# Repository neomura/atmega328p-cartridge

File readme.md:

# neomura/atmega328p-cartridge

Circuit design and games engine for ATMega328P-based cartridges for the Neomura retro games console.

Derived from the [Arduinocade project](https://github.com/rossumur/Arduinocade).

| Link                                         | Description                                                                         |
| -------------------------------------------- | ----------------------------------------------------------------------------------- |
| [License](./license.md)                      | MIT License.                                                                        |
| [Documentation](./documentation/readme.md)   | Documentation regarding this project.                                               |
| [Circuit Design](./circuit-design/readme.md) | KiCad files and assembly instructions for the PCB.                                  |
| [Engine](./engine/readme.md)                 | Source code for the games engine.                                                   |
| [Palette](./palette.aseprite)                | Aseprite palette; each group of four colors is an available palette for a scanline. |

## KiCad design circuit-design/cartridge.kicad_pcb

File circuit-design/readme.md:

# [neomura/atmega328p-cartridge](../readme.md)/Circuit Design

| Link                                         | Description                        |
| -------------------------------------------- | ---------------------------------- |
| [cartridge.pro](./cartridge.pro)             | KiCAD project.                     |
| [cartridge.sch](./cartridge.sch)             | KiCAD schematic.                   |
| [cartridge.kicad_pcb](./cartridge.kicad_pcb) | KiCAD PCB layout.                  |

## Bill of materials

Links are included for reference only and are not endorsements.

| Reference   | Description                                                          | Model No.         | Link                                                                                                                                                                                               |
| ----------- | -------------------------------------------------------------------- | ----------------- | -------------------------------------------------------------------------------------------------------------------------------------------------------------------------------------------------- |
| J1          | Cartridge connector (right-angled 1x15 2.54mm male pin header)       | Unknown           | [https://www.aliexpress.com/item/4000660389713.html?spm=a2g0s.9042311.0.0.65b74c4dMpBmdG](https://www.aliexpress.com/item/4000660389713.html?spm=a2g0s.9042311.0.0.65b74c4dMpBmdG)                 |
| J2          | ICSP header (right-angled 1.5 2.54mm male pin header)                | Unknown           | [https://www.bitsbox.co.uk/index.php?main_page=product_info&cPath=225_230&products_id=3128](https://www.bitsbox.co.uk/index.php?main_page=product_info&cPath=225_230&products_id=3128)             |
| U1          | Microcontroller                                                      | ATMega328P-PU     | [https://www.bitsbox.co.uk/index.php?main_page=product_info&cPath=140_161_162&products_id=1225](https://www.bitsbox.co.uk/index.php?main_page=product_info&cPath=140_161_162&products_id=1225)     |
| X1          | 14.31818MHz (NTSC) or 17.734MHz (PAL 60) HC-49S crystal              | Unknown           | [https://www.aliexpress.com/item/32496964768.html?spm=a2g0s.9042311.0.0.65b74c4dMpBmdG](https://www.aliexpress.com/item/32496964768.html?spm=a2g0s.9042311.0.0.65b74c4dMpBmdG) or [https://www.ebay.co.uk/itm/20pcs-17-734MHz-HC-49S-Crystal-Oscillator-Passive-Quartz-Resonator/253056403948?_trkparms=aid%3D111001%26algo%3DREC.SEED%26ao%3D1%26asc%3D20160908105057%26meid%3D80fd100fd3114f5ba72a3c52a978bf7f%26pid%3D100675%26rk%3D1%26rkt%3D15%26mehot%3Dnone%26sd%3D253056403948%26itm%3D253056403948%26pmt%3D1%26noa%3D1%26pg%3D2380057%26brand%3DUnbranded&_trksid=p2380057.c100675.m4236&_trkparms=pageci%3Ae010b98a-7b73-11eb-b850-3214b911b9a1%7Cparentrq%3Af3c20fd51770a7b3a0b1a3e8fffcf90a%7Ciid%3A1](https://www.ebay.co.uk/itm/20pcs-17-734MHz-HC-49S-Crystal-Oscillator-Passive-Quartz-Resonator/253056403948?_trkparms=aid%3D111001%26algo%3DREC.SEED%26ao%3D1%26asc%3D20160908105057%26meid%3D80fd100fd3114f5ba72a3c52a978bf7f%26pid%3D100675%26rk%3D1%26rkt%3D15%26mehot%3Dnone%26sd%3D253056403948%26itm%3D253056403948%26pmt%3D1%26noa%3D1%26pg%3D2380057%26brand%3DUnbranded&_trksid=p2380057.c100675.m4236&_trkparms=pageci%3Ae010b98a-7b73-11eb-b850-3214b911b9a1%7Cparentrq%3Af3c20fd51770a7b3a0b1a3e8fffcf90a%7Ciid%3A1) |
| R1          | 1M load resistor                                                     | Unknown           | [https://www.bitsbox.co.uk/index.php?main_page=product_info&cPath=83_84_85&products_id=480](https://www.bitsbox.co.uk/index.php?main_page=product_info&cPath=83_84_85&products_id=480)             |
| C1/C2       | 22pF load capacitor                                                  | Unknown           | [https://www.bitsbox.co.uk/index.php?main_page=product_info&cPath=65_75_67&products_id=187](https://www.bitsbox.co.uk/index.php?main_page=product_info&cPath=65_75_67&products_id=187)             |
| D1          | Reset protection diode                                               | 1N4148            | [https://www.bitsbox.co.uk/index.php?main_page=product_info&cPath=140_141_143&products_id=925](https://www.bitsbox.co.uk/index.php?main_page=product_info&cPath=140_141_143&products_id=925)       |
| R2          | 4.7k reset pull-up resistor                                          | Unknown           | [https://www.bitsbox.co.uk/index.php?main_page=product_info&cPath=83_84_85&products_id=452](https://www.bitsbox.co.uk/index.php?main_page=product_info&cPath=83_84_85&products_id=452)             |
| C3          | 100nF reset bypass capacitor                                         | Unknown           | [https://www.bitsbox.co.uk/index.php?main_page=product_info&cPath=65_75_67&products_id=210](https://www.bitsbox.co.uk/index.php?main_page=product_info&cPath=65_75_67&products_id=210)             |
| C4          | 100nF +5V bypass capacitor                                           | Unknown           | [https://www.bitsbox.co.uk/index.php?main_page=product_info&cPath=65_75_67&products_id=210](https://www.bitsbox.co.uk/index.php?main_page=product_info&cPath=65_75_67&products_id=210)             |
| R3          | 470R video carrier resistor                                          | Unknown           | [https://www.bitsbox.co.uk/index.php?main_page=product_info&cPath=83_84_85&products_id=441](https://www.bitsbox.co.uk/index.php?main_page=product_info&cPath=83_84_85&products_id=441)             |
| R4          | 1K video sync resistor                                               | Unknown           | [https://www.bitsbox.co.uk/index.php?main_page=product_info&cPath=83_84_85&products_id=445](https://www.bitsbox.co.uk/index.php?main_page=product_info&cPath=83_84_85&products_id=445)             |
| R5/R7       | 270R audio low-pass resistor                                         | Unknown           | [https://www.bitsbox.co.uk/index.php?main_page=product_info&cPath=83_84_85&products_id=438](https://www.bitsbox.co.uk/index.php?main_page=product_info&cPath=83_84_85&products_id=438)             |
| C5/C7       | 33nF audio low-pass capacitor                                        | Unknown           | [https://www.bitsbox.co.uk/index.php?main_page=product_info&cPath=65_75_67&products_id=208](https://www.bitsbox.co.uk/index.php?main_page=product_info&cPath=65_75_67&products_id=208)             |
| R6/R8       | 150R audio output resistor                                           | Unknown           | [https://www.bitsbox.co.uk/index.php?main_page=product_info&cPath=83_84_85&products_id=435](https://www.bitsbox.co.uk/index.php?main_page=product_info&cPath=83_84_85&products_id=435)             |
| C6/C8       | 10uF audio output capacitor                                          | Unknown           | [https://www.amazon.co.uk/gp/product/B08D647KCD/ref=ppx_yo_dt_b_asin_title_o00_s00?ie=UTF8&psc=1](https://www.amazon.co.uk/gp/product/B08D647KCD/ref=ppx_yo_dt_b_asin_title_o00_s00?ie=UTF8&psc=1) |

### Possible substitutions

#### J1

Right-angled male pin headers appear to come in two distinct styles; one where the plastic retainer is in contact with the PCB, and one where it is instead in contact with the corresponding female socket.  This PCB is designed for the latter, and the former will not fit inside a cartridge shell.

#### J2

In contrast to J1, this must be the style with the plastic retainer in contact with the PCB to fit inside a cartridge shell.  This can be substituted for a vertical pin header (or a socket) if it does not need to fit inside a cartridge shell.

#### U1

Other pin-compatible ATMega ICs may work.  Note that most will have smaller flash space and may not be able to store complex games.

#### X1/R1/C1/C2

Most 14.31818MHz crystals which are HC49 or smaller will work as long as appropriate bypass capacitors and resistor are included.  To be compatible with Arduinocade games instead of Neomura games, a 28.6363MHz crystal such as [https://www.aliexpress.com/item/32910067235.html?spm=a2g0s.9042311.0.0.5bfd4c4d3a2EOO](https://www.aliexpress.com/item/32910067235.html?spm=a2g0s.9042311.0.0.5bfd4c4d3a2EOO) may be used instead.

It may be possible to omit the load resistor.

#### D1

This diode is included to prevent accidental high-voltage programming.  It can be omitted.

## Assembly instructions

- Start by soldering J1 and J2.  I would recommend using some kind of clamp such as a crocodile clip to keep it firmly attached to the board (note that it will act as a heatsink, making soldering more difficult, if in contact with pins).  Use short bursts of high heat and allow time to cool between joints to avoid melting the plastic retainer.  After soldering, use a female socket to ensure that pins are straight, and use said female socket to correct the pins if not parallel with the PCB.
- Solder all other components.  There is not much room inside the shell once constructed, so ensure that these are as close to the board top as possible and that leads are clipped short.
- Place the PCB, logo up, into the back half of the shell.
- Place the front half of the shell on top and press fit.  Be careful to ensure that no components will be crushed, such as C1 and C2; you may need to stand these at 45 degrees to avoid contact with the front half of the case.

### Program

J2 is all pins except VCC of a standard 2x3 ICSP header.  These have been arranged to match pins 10-13 of an Arduino used as a programmer.

If using an [Arduino as an ISP](https://www.arduino.cc/en/Tutorial/BuiltInExamples/ArduinoISP), connect the following pins (where the Arduino has multiple pins labelled the same, any will work):

| Arduino | ICSP  |
| ------- | ----- |
| GND     | GND.  |
| 5V      | VCC.  |
| 13      | SCK.  |
| 12      | MISO. |
| 11      | MOSI. |
| 10      | RST.  |

#### Set fuse bits

By default, an ATMega328P will use its internal 8MHz clock rather than an external crystal.  To configure this, use [AVRDUDE](https://www.nongnu.org/avrdude/) to set the correct fuse bits:

```shell
avrdude -pM328P -Ulfuse:w:0xf7:m -Uhfuse:w:0xde:m -Uefuse:w:0xfd:m
```

Note that you will need to add command line arguments to this to specify which programmer you are using, for example:

| Programmer                                 | Suffix                         |
| ------------------------------------------ | ------------------------------ |
| USBtiny                                    | -cusbtiny                      |
| Arduino as ISP on COM port 3 under Windows | -cavrisp -b 19200 -Pcom3       |
| Arduino as ISP on COM port 3 under Linux   | -cavrisp -b 19200 -P/dev/ttyS3 |

If you are running AVRDUDE under Windows Subsystem for Linux, you may find that the remapped COM ports do not work.  In these instances, running AVRDUDE under Windows at least once seems to resolve this.

You may see an error that the extended fuse could not be written.  This is normal, as not all of its bits are writable; it could be argued to be more of an AVRDUDE bug that it tried to check them.

#### Flash

Next, write a program to flash.  Make sure that a .hex file to write exists in the current working directory, then execute:

```shell
avrdude -pM328P -Uflash:w:name-of-your-hex-file.hex
```

As before, you will need to add command line arguments to specify the correct programmer.

After following these steps, you should be able to connect the video pin (cartridge left 1) to the composite video input on a NTSC-compatible display and see a picture.

## References

| Link                                                                                                                                                     | Description                            |
| -------------------------------------------------------------------------------------------------------------------------------------------------------- | -------------------------------------- |
| [https://www.instructables.com/Adding-ICSP-header-to-your-ArduinoAVR-board/](https://www.instructables.com/Adding-ICSP-header-to-your-ArduinoAVR-board/) | Source for ICSP header layout.         |
| [https://www.arduino.cc/en/Tutorial/BuiltInExamples/ArduinoISP](https://www.arduino.cc/en/Tutorial/BuiltInExamples/ArduinoISP)                           | Details on using an Arduino as an ISP. |
| [https://forum.arduino.cc/index.php?topic=71580.0](https://forum.arduino.cc/index.php?topic=71580.0)                                                     | Source for default Arduino fuses.      |
| [https://www.avrfreaks.net/forum/unable-reset-fuses-atmega328p](https://www.avrfreaks.net/forum/unable-reset-fuses-atmega328p)                           | Workaround for AVRDUDE problem.        |
| [https://www.ladyada.net/learn/avr/avrdude.html](https://www.ladyada.net/learn/avr/avrdude.html)                                                         | AVRDUDE instructions.                  |

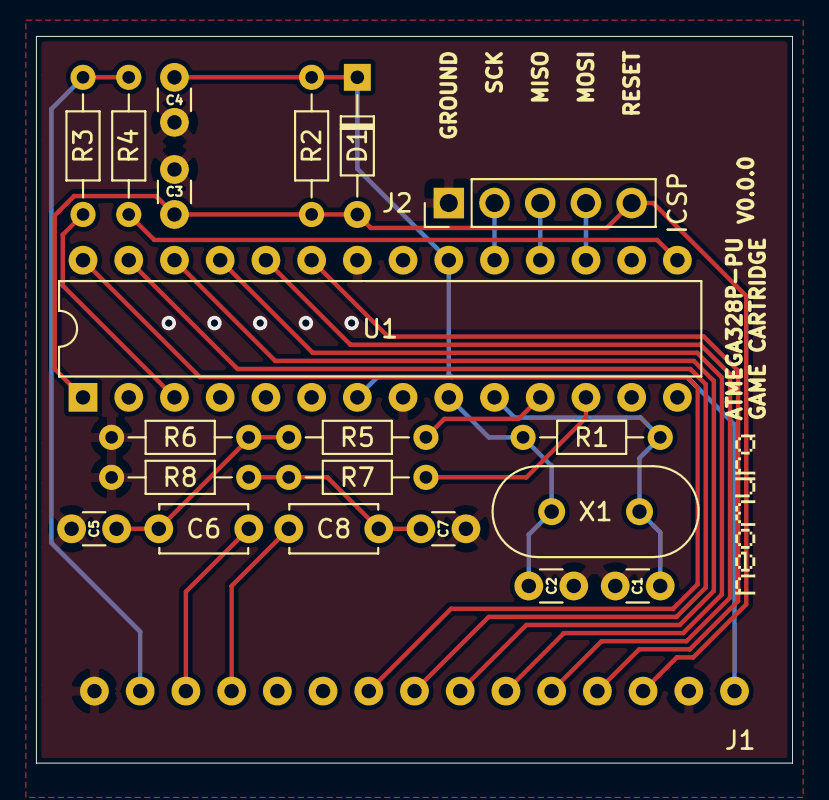
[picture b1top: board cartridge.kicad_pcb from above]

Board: 2 copper layers, 42.0 x 40.4 mm, 22 parts (0 on the bottom side), 23 nets.

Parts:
C1, C2: 22pF; C_Disc_D3.0mm_W1.6mm_P2.50mm
C3, C4: 100nF; C_Disc_D3.0mm_W1.6mm_P2.50mm
C5, C7: 33n; C_Disc_D3.0mm_W1.6mm_P2.50mm
C6, C8: 10uF; C_Disc_D4.7mm_W2.5mm_P5.00mm
D1: 1N4148; D_DO-34_SOD68_P7.62mm_Horizontal
J1: Connector; Cartridge
J2: ICSP; PinHeader_1x05_P2.54mm_Vertical
R1: 1M; R_Axial_DIN0204_L3.6mm_D1.6mm_P7.62mm_Horizontal
R2: 4.7K; R_Axial_DIN0204_L3.6mm_D1.6mm_P7.62mm_Horizontal
R3: 470R; R_Axial_DIN0204_L3.6mm_D1.6mm_P7.62mm_Horizontal
R4: 1K; R_Axial_DIN0204_L3.6mm_D1.6mm_P7.62mm_Horizontal
R5, R7: 270R; R_Axial_DIN0204_L3.6mm_D1.6mm_P7.62mm_Horizontal
R6, R8: 150R; R_Axial_DIN0204_L3.6mm_D1.6mm_P7.62mm_Horizontal
Ref**: Val**; Front-Silkscreen
U1: ATmega328P-PU; DIP-28_W7.62mm
X1: 14.31818MHz (NTSC) or 17.734MHz (PAL 60); Crystal_HC49-4H_Vertical

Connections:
+5V: C4.1, D1.1, J1.15, R2.1, U1.7, U1.20
AUDIO_L: C6.1, J1.3
AUDIO_PWM_L: R5.2, U1.11
AUDIO_PWM_R: R7.2, U1.12
AUDIO_R: C8.1, J1.4
GND: C1.1, C2.2, C3.2, C4.2, C5.1, C7.1, J1.1, J1.14, J2.1, R6.2, R8.2, U1.8, U1.22
MISO: J2.3, U1.18
MOSI: J2.4, U1.17
unnamed: C5.2, C6.2, R5.1, R6.1
unnamed: C7.2, C8.2, R7.1, R8.1
PAD_0_DATA: J1.9, U1.26
PAD_1_DATA: J1.10, U1.25
PAD_2_DATA: J1.11, U1.24
PAD_3_DATA: J1.12, U1.23
PAD_CLOCK: J1.8, U1.27
PAD_LATCH: J1.7, U1.28
RESET: C3.1, D1.2, J1.13, J2.5, R2.2, U1.1
SCK: J2.2, U1.19
VIDEO: J1.2, R3.2, R4.1
VIDEO_CARRIER: R3.1, U1.3
VIDEO_HSYNC: R4.2, U1.15
XTAL1: C2.1, R1.2, U1.9, X1.2
XTAL2: C1.2, R1.1, U1.10, X1.1

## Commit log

2021-01-31 Initial commit.
2021-02-02 Fix wording.
2021-02-02 Explain why we use OC1A.
2021-02-02 Finish sentence.
2021-02-02 Fix link.
2021-02-02 Document how vertical sync is generated.
2021-02-03 Document post-assembly instructions.
2021-02-06 Update submodules/neomura/cartridge commit hash to d9b84b3
2021-02-06 Update submodules/neomura/logo commit hash to dd328d1
2021-02-09 Update submodules/neomura/cartridge commit hash to f92c562
2021-02-09 Update submodules/neomura/logo commit hash to b979524
2021-02-09 Update submodules.
2021-02-10 Add initial version of circuit design.
2021-02-10 Fix missing file.
2021-02-11 Update submodules/neomura/cartridge commit hash to 0f45726
2021-02-11 Update footprints.
2021-02-13 Update BOM and assembly instructions.
2021-02-13 Document progressive scan.
2021-02-13 Move documentation.
2021-02-17 Update submodules/neomura/cartridge commit hash to a232597
2021-02-20 Redesign; uses the new cartridge connector, a smaller crystal, ICSP header, and improved audio.
2021-02-20 Document audio.
2021-02-20 Add reference for offset voltages being fine.
2021-02-20 Fix fuse documentation.
2021-02-22 Correct resistor reading.
2021-02-23 Measure real components and update schematic/PCB layout to match. This version was sent to prototype manufacturing.
2021-02-23 Document WSL problems.
2021-02-26 Update documentation to detail out-of-spec VSYNC pulses.
2021-02-26 Update palettes based upon observations of real circuit.
2021-03-06 Documentation rewrite.
2021-03-06 Add PAL 60 crystals to BOM and schematic.
2021-03-21 Adjust resolution based on tests.
2021-03-21 Begin building out drivers.
2021-03-23 Fix typo.
2021-03-26 Switch to full swing oscillator mode.
2021-03-26 Document AVRDUDE bug.
2021-03-27 Add warning regarding case interference.
2021-03-27 Implement basic audio synthesis.
2021-03-27 Fix typos.
2021-03-27 Rename macro.
2021-04-02 Remove unnecessary store.
2021-04-02 Fix broken example.
2021-04-02 Fix wrong lines being read from (this was masked by a bug in the NTSC driver).
2021-04-02 Swap again.
2021-04-02 Add a helper for drawing a point.
2021-04-02 Link to the point routine.
2021-04-02 Fix readme errata.
2021-04-02 Add a number of utility functions.
2021-04-02 Implement the NTSC TV standard.
2021-04-02 Add the main loop.
2021-04-08 Move utilities to after globals.
2021-04-08 Fix pads not being initialized.
2021-04-08 Fix long game_frame implementations causing build errors.
2021-04-09 Add engine readme.
2021-04-09 Begin formalizing the engine.
2021-04-09 Add readmes.
2021-04-09 Grammar improvement.
2021-04-09 Fix links.
2021-04-09 Remove obsolete note.
2021-04-09 Formatting.
2021-04-09 Add missing links to audio.
2021-04-10 Formatting improvements.
2021-04-10 Revise circuit design to remove (potentially dangerous) ICSP VCC pin and remove the need for an adapter to an Arduino.
2021-04-10 Add utility macros for loading/storing words.
2021-04-10 Implement pad polling.
2021-04-10 Fix inconsistent casing.
2021-04-10 Add defs for general purpose registers.
2021-04-10 Large overhaul to reduce round-trips to SRAM.
2021-04-11 Restructure of engine to use includes for easier jmping.
2021-04-11 Readme amendments.
2021-04-11 Move pad polling into the TV interrupt - this is both much smaller in instruction count now by the order of hundreds of bytes, and pads are polled during the active video lines, which means they won'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
2021-04-11 Begin merging TV standard drivers.
2021-04-14 Significant overhaul of the engine to remove the driver concept.
2021-04-14 Add buildable example.
2021-04-14 Fix grammar.
2021-04-14 Clarify palette switching.
2021-04-14 Calculate timing offset rather than applying it.
2021-04-14 Fix interrupt flags not being initialized.
2021-04-14 Allow for video standard specific timing offsets.
2021-04-14 Implement PAL 60.
2021-04-14 Update submodules/neomura/cartridge commit hash to 0b4005f
2021-04-14 Get back a little more main loop time on PAL 60.
2021-04-14 Document PAL 60.
2021-04-14 Add build in CI.
2021-04-14 Rename job.
2021-04-14 Fix working directory.
2021-04-15 Update submodules/neomura/cartridge commit hash to b22c4fe
2021-04-17 Fix comment.
2021-04-17 Add LUT helper.
2021-04-17 Move utilities into a subdirectory.
2021-04-17 Add a zero register.
2021-04-17 Redesign the LUT helper.
2021-04-17 Fix broken paths.
2021-04-18 Make transparency colors transparent in the palette.
2022-03-07 Update actions/checkout action to v3
